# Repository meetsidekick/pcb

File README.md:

# pcb

This project follows the [Pride Versioning Scheme](https://pridever.org)! Current Version: `v0.5.1`. The latest version can be found on the releases page along with gerber files. 

## Open Locally(KiCad)

> [!WARNING]
> Recursive is important as we use many submodules! If you forget to do this, ensure that you run the 3rd command from here where we run `git submodule update --init --recursive`

```bash
git clone https://github.com/MeetSidekick/pcb --recursive sidekick-pcb
```

```bash
cd sidekick-pcb
```

```bash
git submodule update --init --recursive
```

Now open KiCad, navigate to `File` -> `Open Project` and select this project. 

> [!TIP]
> We have recently migrated from the old repo, please use this. The releases prior to `v0.5.1` can be found at: https://github.com/MakerSidekick/pcb/releases/

## Assets

### Render

### PCB

### Schematics 

[Click here for a link to schematics sheet, PDF](assets/sidekick-schematics.pdf)

### 3D View

[CLick here to open(step file)](assets/3d/sidekick.glb)

## License
<a href="https://github.com/MakerSidekick/pcb/">Sidekick (PCB Files)</a> © 2025 by <a href="https://sounddrill31.github.io">Souhrud Reddy</a> is licensed under <a href="https://creativecommons.org/licenses/by-sa/4.0/">CC BY-SA 4.0</a>

This license does not include/grant some files/folders under this repository. They will be mentioned in the next section. 
### License Exceptions and External Credits
The following folders are not included in the license mentioned above! These may be related or required to use the project.
#### Folder: PCBCUPID-SYS-FTP-STP
Used: Glyph C3 3D model, symbol and footprint. This is copyright of [pcbcupid](https://pcbcupid.com/), found publicly at: https://github.com/pcbcupid/PCBCUPID-SYS-FTP-STP

#### Folder: usini-sensors
Used: ADXL345 3d model, footprint, and symbol. This is copyright of [µsini](https://usini.eu/), found publicly at: https://github.com/usini/usini_kicad_sensors/blob/e2d03afffcb95ee2b2ff4183b6573658f2684229/usini_sensors.pretty/adxl345.step

Note:
- The 3d design is licensed under Creative Commons 0 by the same author, as per the README on the repository above, found publicly at: https://grabcad.com/library/adxl345-breakout-board-1

#### Folder: SnapEDA-Downloads
Used: DM-OLED096-636 3d model, footprint, and symbol. This is copyright of [SnapEDA](https://www.snapeda.com), found publicly at: https://www.snapeda.com/parts/DM-OLED096-636/Display%20Module/view-part/?ref=search&t=%20DM-OLED096-636%20&ab_test_case=b

Note: 
- According to the official FAQ, these seem to be licensed under Creative Commons Attribution-ShareAlike 4.0 International License (CC BY-SA) along with Design Exception 1.0. Link to the FAQ: https://www.snapeda.com/about/FAQ/

#### Folder: tg9541-modules
Used: None. TODO: Remove.

#### Folder: Glyph-C3
Used: none. TODO: Remove.

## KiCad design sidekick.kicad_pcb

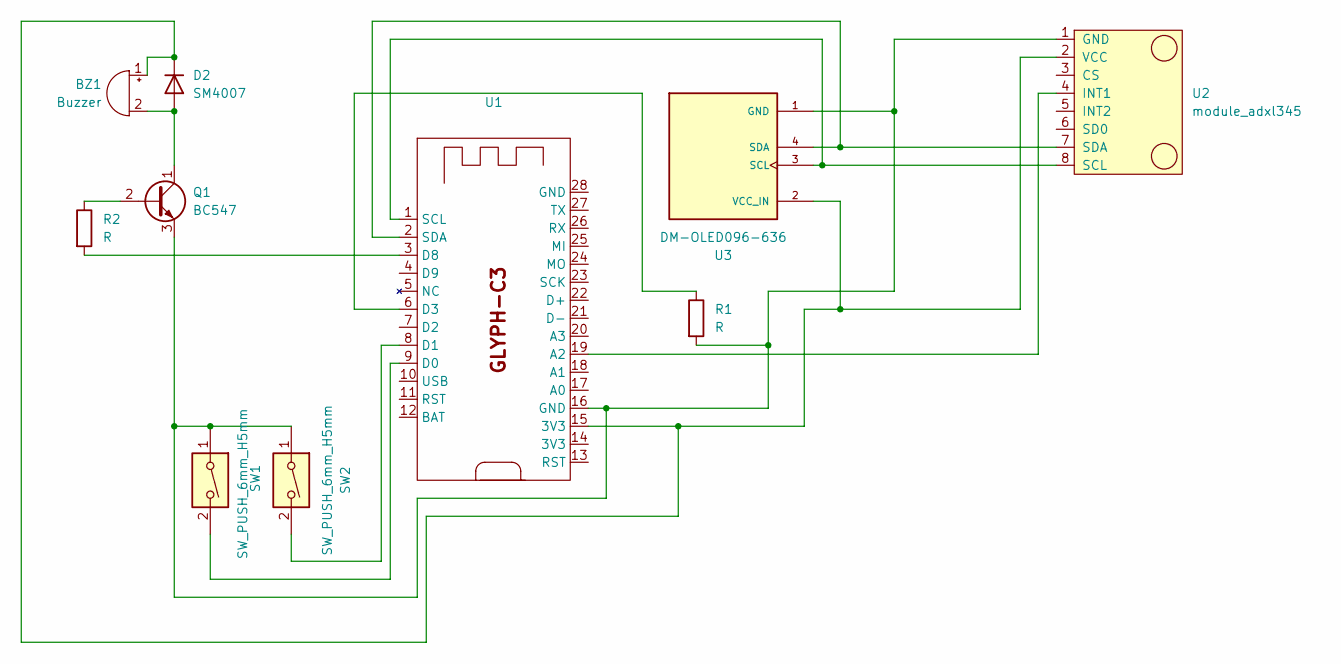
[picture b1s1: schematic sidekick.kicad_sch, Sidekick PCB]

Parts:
BZ1: Buzzer; Buzzer_12x9.5RM7.6
D2: SM4007; D_MELF
Q1: BC547; TO-92_Inline
R1: R; R_Axial_DIN0207_L6.3mm_D2.5mm_P7.62mm_Horizontal
R2: R; R_Axial_DIN0204_L3.6mm_D1.6mm_P5.08mm_Horizontal
SW1, SW2: SW_PUSH_6mm_H5mm
U1: GlyphC3; PARTREV v1.0
U2: module_adxl345
U3: DM-OLED096-636; MODULE_DM-OLED096-636; PARTREV 2018-09-10

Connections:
unnamed 0: BZ1.1 (+), D2.1 (K), U1.15 (3V3), U2.2 (VCC), U3.2 (GND); also elsewhere on the board
unnamed: BZ1.2 (-), D2.2 (A), Q1.1 (C)
unnamed: Q1.2 (B), R2.1
unnamed 3: Q1.3 (E), R1.2, SW1.1, SW2.1, U1.16 (GND), U2.1 (GND), U3.1 (VCC_IN); also elsewhere on the board
unnamed: U1.19 (A2), U2.4 (INT1)
unnamed: SW1.2, U1.9 (D0)
unnamed: SW2.2, U1.8 (D1)
unnamed: R1.1, U1.6 (D3)
unnamed: R2.2, U1.3 (D8)
unnamed 9: U1.1 (SCL), U2.8 (SCL), U3.3 (SCL); also elsewhere on the board
unnamed 10: U1.2 (SDA), U2.7 (SDA), U3.4 (SDA); also elsewhere on the board

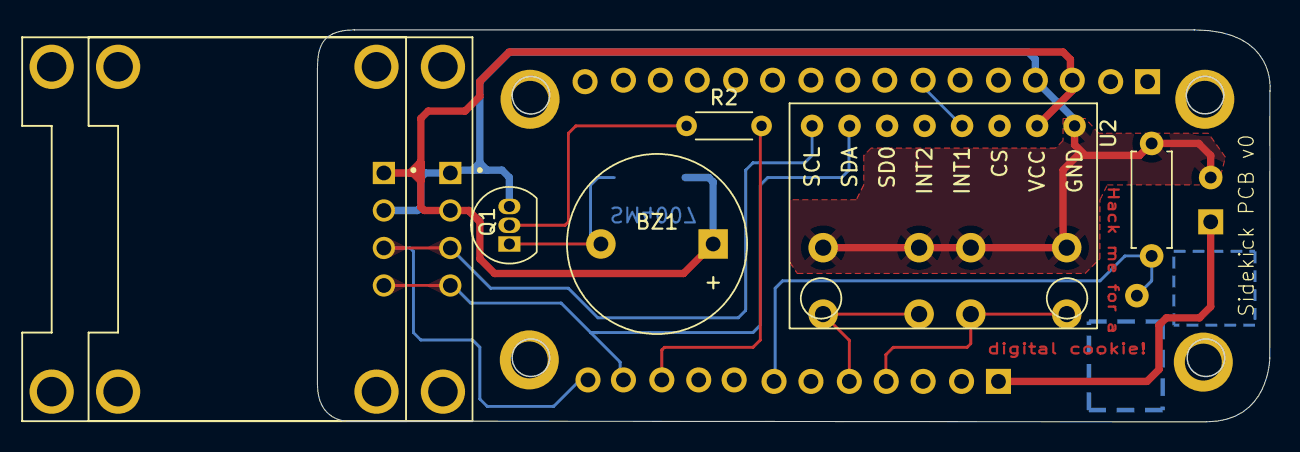
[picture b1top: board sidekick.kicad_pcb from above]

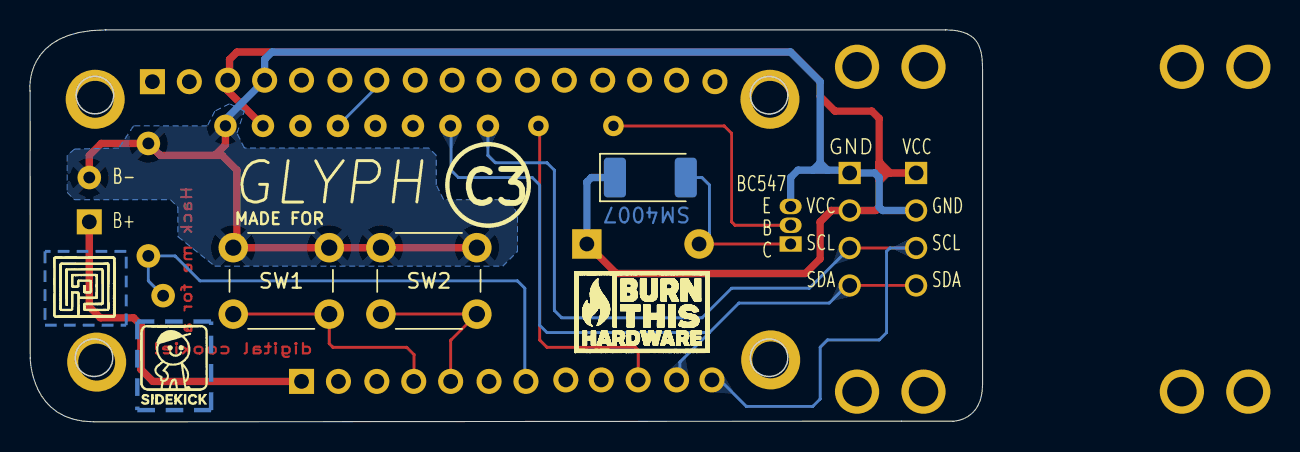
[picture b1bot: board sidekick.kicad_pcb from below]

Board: 2 copper layers, 64.5 x 26.5 mm, 11 parts (3 on the bottom side), 11 nets.

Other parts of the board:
U3#2: DM-OLED096-636; MODULE_DM-OLED096-636

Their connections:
unnamed 0: U3#2.2 (VCC_IN); also elsewhere on the board
unnamed 3: U3#2.1 (GND); also elsewhere on the board
unnamed 9: U3#2.3 (SCL); also elsewhere on the board
unnamed 10: U3#2.4 (SDA); also elsewhere on the board

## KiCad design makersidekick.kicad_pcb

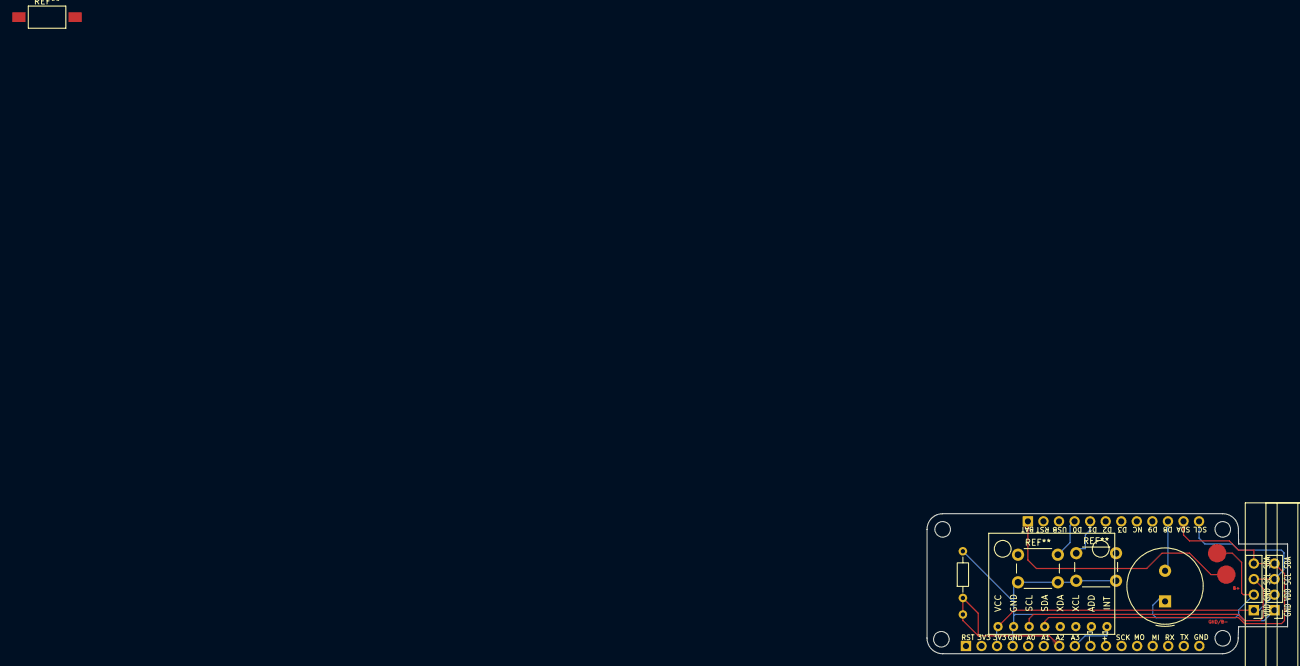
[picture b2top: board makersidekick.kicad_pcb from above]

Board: 2 copper layers, 58.9 x 22.9 mm, 4 parts (1 on the bottom side), 4 nets.

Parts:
Display 128x64 0.96" I2C, Display 128x64 0.96" I2C#2: Display_128x64; Display_128x64_096_I2C
J2: Conn_01x12; PinSocket_1x12_P2.54mm_Vertical
J4: Conn_01x16; PinSocket_1x16_P2.54mm_Vertical

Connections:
3v3: Display 128x64 0.96" I2C.2, Display 128x64 0.96" I2C#2.1, J4.3
SCL: Display 128x64 0.96" I2C.3, Display 128x64 0.96" I2C#2.3, J2.12
SDA: Display 128x64 0.96" I2C.4, Display 128x64 0.96" I2C#2.4, J2.11
gnd: Display 128x64 0.96" I2C.1, Display 128x64 0.96" I2C#2.2, J4.4

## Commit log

2025-08-11 Initial repo
2025-08-11 Add project files
2025-08-11 Add pcbcupid to submodules
2025-08-11 Add hardware, almost finalize routing TODO: actually finish the pins
2025-08-11 Add header pins to schematic(initial)
2025-08-12 Add screenshots of pcb onto the readme
2025-08-12 Assign nets, finish connection, prep for v0
2025-08-12 Add buttons, shift text and reroute a lot
2025-08-13 Upload new template project We will be doing this again properly
2025-08-13 Add schematic and placeholder pcb
2025-08-13 Cleanup
    update
2025-08-13 Reupload website
2025-08-13 Prepare for v0.3.0
2025-08-13 Bump to v0.3.0 - Add filled zones for GND, add thicker traces for VCC - Add Battery pins - Fix label alignment for display
2025-08-14 Bump to v0.3.7 (yet to upload)
2025-08-14 Upload v0.3.7 contents
2025-08-14 Add render images for v0.3.7
2025-08-14 Bump to v0.3.8
2025-08-14 Mention bump to v0.3.8
2025-08-14 Fix link to pcb
2025-08-14 v0.3.8: Add pins text for BJT
2025-08-14 Version v0.3.9
2025-08-14 Version 0.4!
2025-08-14 Revision v0.4.2
2025-08-15 Bump to v0.4.8
2025-08-15 Credit mono
2025-08-15 Credit google
2025-08-15 Fix credits text
2025-08-15 Attempt to improve loading speed
2025-08-15 Simplify
2025-08-15 Try to redo animations
2025-08-16 Decrease glb size
2025-08-16 Add gltfpack-ed model
2025-08-16 small model
2025-08-16 Try to fix broken site info, and update page
2025-08-16 Improve alignment, fix overflow
2025-08-16 Hide hotspots for now
2025-08-16 Bump to v0.4.9
2025-08-17 License under CC BY-SA 4.0
2025-08-17 Fix image links!
2025-08-17 Bump to 0.5.1
2025-08-17 Regenerate models
2025-08-18 Migrate
2025-08-21 Improve tooling
2025-08-21 Try to improve pcb model
2025-08-21 make kicad install smaller
2025-08-22 Pack after both files are generated
2025-08-22 Allow it to continue after export
2025-08-22 Ensure it runs twice if it fails
2025-08-22 Auto-export GLB files and optimize with gltfpack
2025-08-26 Bring back --include-pads --include-zones
2025-08-26 Disable fuse shapes
2025-08-26 Use submodules too
2025-09-09 Change GitHub repository URL in README
    Updated the repository URL in the README to reflect the new GitHub organization.
2025-09-09 Fix repository link and update README content
    Updated repository link and removed warning about work in progress.
2025-09-14 Generate step as well
